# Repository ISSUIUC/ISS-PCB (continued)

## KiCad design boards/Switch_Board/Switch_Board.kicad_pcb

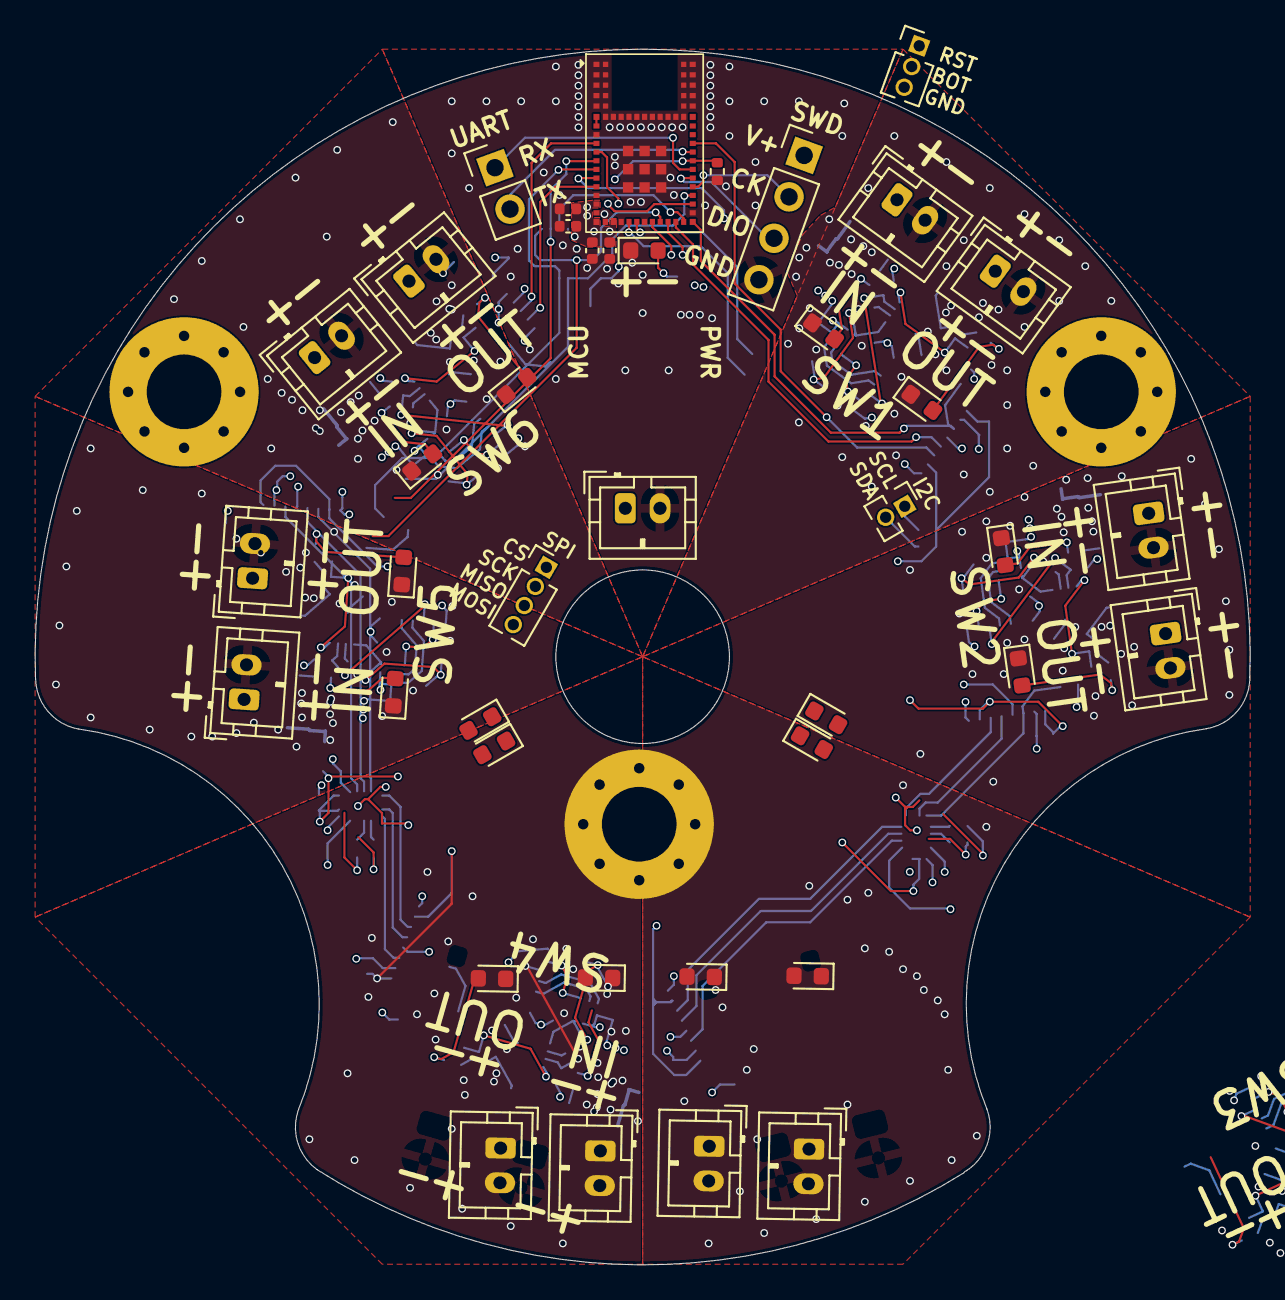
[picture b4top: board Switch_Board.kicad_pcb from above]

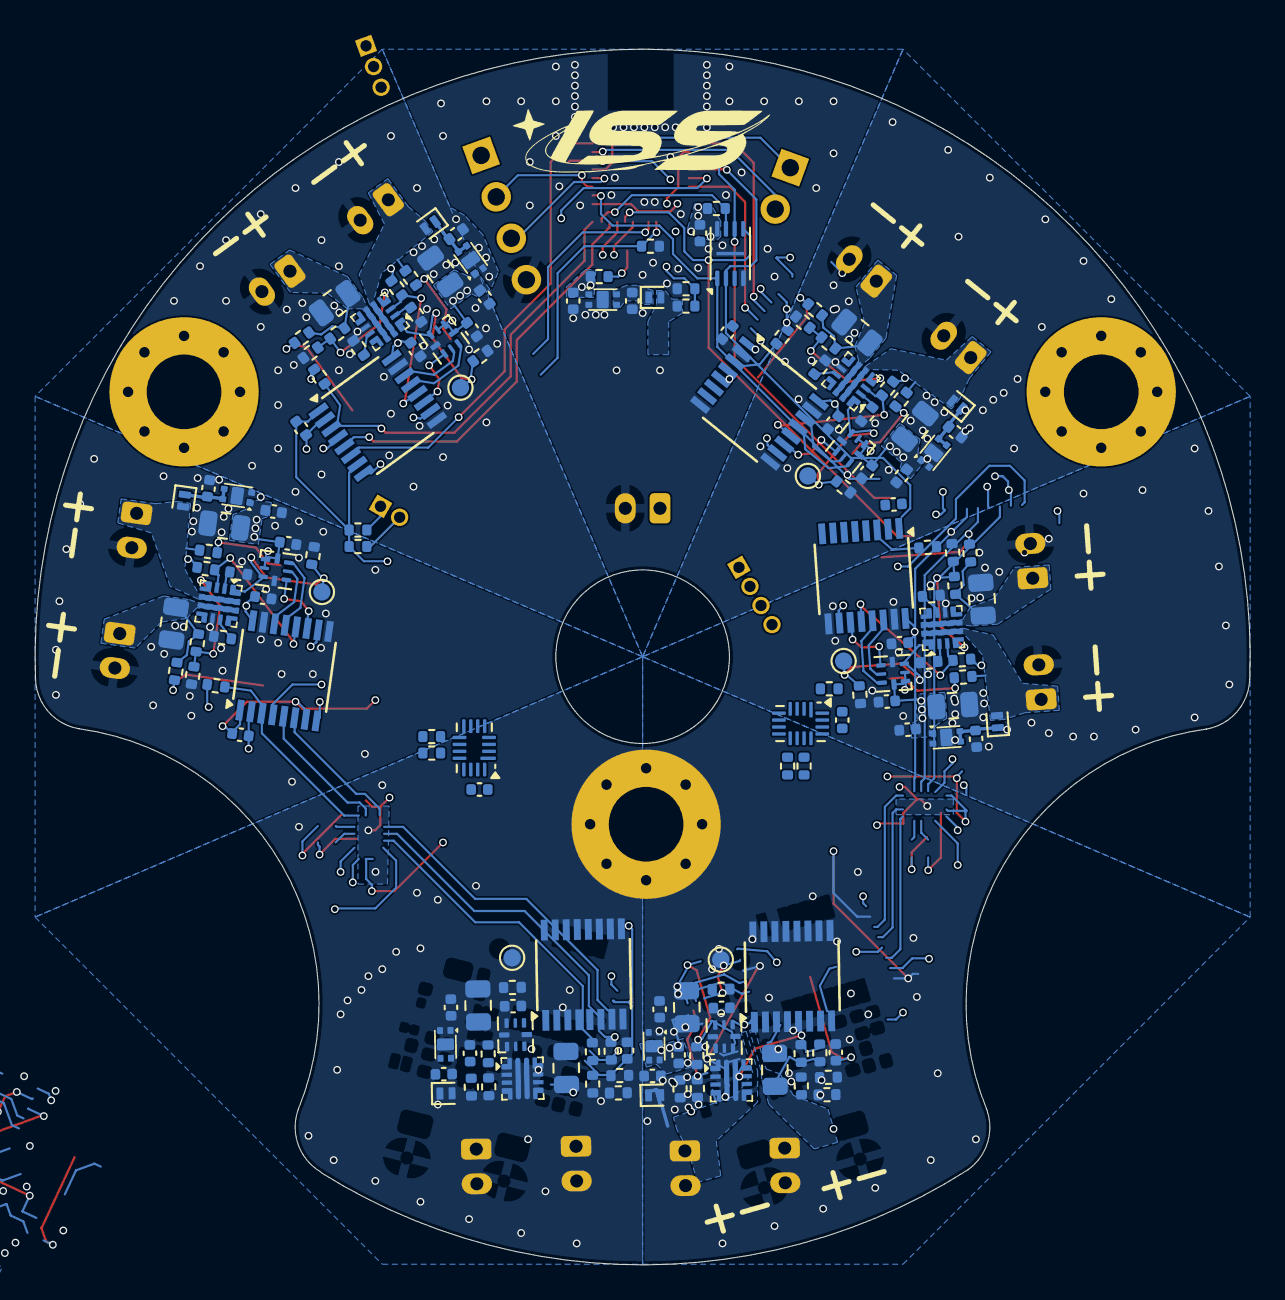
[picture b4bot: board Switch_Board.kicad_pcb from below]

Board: 4 copper layers, 70.0 x 70.0 mm, 198 parts (154 on the bottom side), 138 nets.

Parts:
C101, C103, C104, C105, C108, C109, C201, C202, C203, C301, C302, C303, C401, C402, C403, C501, C502, C503, C601, C602, C603, C701, C702, C703: 100nF; C_0402_1005Metric
C102, C107: 4.7uF; C_0402_1005Metric
C106, C204, C205, C304, C305, C404, C405, C504, C505, C604, C605, C704, C705: 1uF; C_0402_1005Metric
C206, C306, C406, C506, C606, C706: 100uF; C_0805_2012Metric
C207, C307, C407, C507, C607, C707: 22uF; C_0805_2012Metric
D101, D201, D301, D401, D501, D601, D701: SDM05U40CSP-7; D_SOD-882
D102, D103, D202, D302, D402, D502, D602, D702: RED; LED_0603_1608Metric
D104: ORANGE; LED_0603_1608Metric
D105, D203, D303, D403, D503, D603, D703: GREEN; LED_0603_1608Metric
D106: BLUE; LED_0603_1608Metric
H101, H102, H103: MountingHole_Pad; MountingHole_4.3mm_M4_Pad_Via
J101: Conn_01x03; PinHeader_1x03_P1.27mm_Vertical
J102: Conn_01x04; PinHeader_1x04_P2.54mm_Vertical
J103, J201, J203, J301, J303, J401, J403, J501, J503, J601, J603, J701, J703: Conn_01x02; JST_PH_B2B-PH-K_1x02_P2.00mm_Vertical
J104: Conn_01x02; PinHeader_1x02_P2.54mm_Vertical
J105: Conn_01x02; PinHeader_1x02_P1.27mm_Vertical
J106: Conn_01x04; PinHeader_1x04_P1.27mm_Vertical
J202, J302, J402, J502, J602, J702: Conn_01x01; TestPoint_Pad_D1.0mm
R101, R102, R103, R113, R201, R202, R204, R301, R302, R304, R401, R402, R404, R501, R502, R504, R601, R602, R604, R701, R702, R704: 10k; R_0402_1005Metric
R104, R105, R106, R107, R108: 470; R_0402_1005Metric
R109, R112: 4.7k; R_0402_1005Metric
R110, R111: 100k; R_0402_1005Metric
R203, R209, R303, R309, R403, R409, R503, R509, R603, R609, R703, R709: 1k; R_0402_1005Metric
R205, R305, R405, R505, R605, R705: 680; R_0402_1005Metric
R206, R306, R406, R506, R606, R706: 390k; R_0402_1005Metric
R207, R307, R407, R507, R607, R707: 300k; R_0402_1005Metric
R208, R308, R408, R508, R608, R708: 500k; R_0402_1005Metric
U101: W25Q16JLUX; Winbond_USON-8-1EP_3x2mm_P0.5mm_EP0.2x1.6mm
U102: STM32WB1MMC; LGA77_6P5X10_STM
U103, U203, U303, U403, U503, U603, U703: XC6223; Torex_USP-4
U104, U105: TCAL9538; UQFN-16_1.8x2.6mm_P0.4mm
U201, U301, U401, U501, U601, U701: ISO7742; SSOP-16_3.9x4.9mm_P0.635mm
U202, U302, U402, U502, U602, U702: SN74AUP1G74RSER; UQFN-RSE0008A
U204, U304, U404, U504, U604, U704: TPS25947; VQFN-HR-RPW0010A

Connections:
/BLUE_LED: R108.1, U105.10 (P7)
/BOOT: J101.2, R102.2, U102.22 (BOOT0)
/CoinCell_V: D101.2 (A), J103.1, R110.2
/EXP_RESET: R103.1, U102.13 (PA2), U104.1 (~RESET), U105.1 (~RESET)
/FLASH_CS: J106.1, U101.1 (~CS), U102.33 (PB4)
/FLASH_RESET: R101.2, U101.7 (~HOLD/~RESET/IO_{3}), U102.29 (PA7)
/GPIO_Clock: R113.2, U102.37 (PA0), U201.4 (INB), U301.4 (INB), U401.4 (INB), U501.4 (INB), U601.4 (INB), U701.4 (INB)
/GREEN_LED: R107.1, U105.9 (P6)
/I2C_SCL: J105.1, R112.1, U102.27 (PB6), U104.12 (SCL), U105.12 (SCL)
/I2C_SDA: J105.2, R109.1, U102.25 (PB7), U104.13 (SDA), U105.13 (SDA)
/NRST: J101.1, U102.23 (NRST)
/ORANGE_LED: R106.1, U104.10 (P7)
/PG_ISO_1: U102.28 (PA3), U201.5 (OUTC)
/PG_ISO_2: U104.7 (P4), U301.5 (OUTC)
/PG_ISO_3: U104.3 (P1), U401.5 (OUTC)
/PG_ISO_4: U105.7 (P4), U501.5 (OUTC)
/PG_ISO_5: U105.3 (P1), U601.5 (OUTC)
/PG_ISO_6: U102.9 (PA4), U701.5 (OUTC)
/RED_LED: R105.1, U104.9 (P6)
/SPI_MISO: J106.3, U101.2 (DO/IO_{1}), U102.12 (PA6)
/SPI_MOSI: J106.4, U101.5 (DI/IO_{0}), U102.26 (PB5)
/SPI_SCK: J106.2, U101.6 (CLK), U102.11 (PA1)
/SWCLK: J102.2, U102.34 (PA14)
/SWDIO: J102.3, U102.35 (PA13)
/Switch 1/PG: R204.2, U201.12 (INC), U204.3 (PG/AUXOFF)
/Switch 1/Q: J202.1, R202.2, U202.3 (Q), U204.1 (EN/UVLO)
/Switch 1/Reg_V: C201.1, C203.1, C205.1, C206.1, R204.1, U201.10 (EN2), U201.16 (VCC2), U202.1 (~PRE), U202.2 (~CLR), U202.8 (VCC), U203.1 (VOUT)
/Switch 1/SubBatt_GND: C201.2, C203.2, C204.2, C205.2, C206.2, C207.2, D202.1 (K), D203.1 (K), J201.2, J203.2, R202.1, R205.1, R206.2, R208.2, U201.9 (GND2), U201.15 (GND2), U202.4 (GND), U203.2 (VSS), U203.5 (EP), U204.8 (GND)
/Switch 1/SubBatt_V: D201.2 (A), J201.1, R203.1, U204.5 (IN)
/Switch 1/~Q: U201.11 (IND), U202.5 (~Q)
/Switch 2/PG: R304.2, U301.12 (INC), U304.3 (PG/AUXOFF)
/Switch 2/Q: J302.1, R302.2, U302.3 (Q), U304.1 (EN/UVLO)
/Switch 2/Reg_V: C301.1, C303.1, C305.1, C306.1, R304.1, U301.10 (EN2), U301.16 (VCC2), U302.1 (~PRE), U302.2 (~CLR), U302.8 (VCC), U303.1 (VOUT)
/Switch 2/SubBatt_GND: C301.2, C303.2, C304.2, C305.2, C306.2, C307.2, D302.1 (K), D303.1 (K), J301.2, J303.2, R302.1, R305.1, R306.2, R308.2, U301.9 (GND2), U301.15 (GND2), U302.4 (GND), U303.2 (VSS), U303.5 (EP), U304.8 (GND)
/Switch 2/SubBatt_V: D301.2 (A), J301.1, R303.1, U304.5 (IN)
/Switch 2/~Q: U301.11 (IND), U302.5 (~Q)
/Switch 3/PG: R404.2, U401.12 (INC), U404.3 (PG/AUXOFF)
/Switch 3/Q: J402.1, R402.2, U402.3 (Q), U404.1 (EN/UVLO)
/Switch 3/Reg_V: C401.1, C403.1, C405.1, C406.1, R404.1, U401.10 (EN2), U401.16 (VCC2), U402.1 (~PRE), U402.2 (~CLR), U402.8 (VCC), U403.1 (VOUT)
/Switch 3/SubBatt_GND: C401.2, C403.2, C404.2, C405.2, C406.2, C407.2, D402.1 (K), D403.1 (K), J401.2, J403.2, R402.1, R405.1, R406.2, R408.2, U401.9 (GND2), U401.15 (GND2), U402.4 (GND), U403.2 (VSS), U403.5 (EP), U404.8 (GND)
/Switch 3/SubBatt_V: D401.2 (A), J401.1, R403.1, U404.5 (IN)
/Switch 3/~Q: U401.11 (IND), U402.5 (~Q)
/Switch 4/PG: R504.2, U501.12 (INC), U504.3 (PG/AUXOFF)
/Switch 4/Q: J502.1, R502.2, U502.3 (Q), U504.1 (EN/UVLO)
/Switch 4/Reg_V: C501.1, C503.1, C505.1, C506.1, R504.1, U501.10 (EN2), U501.16 (VCC2), U502.1 (~PRE), U502.2 (~CLR), U502.8 (VCC), U503.1 (VOUT)
/Switch 4/SubBatt_GND: C501.2, C503.2, C504.2, C505.2, C506.2, C507.2, D502.1 (K), D503.1 (K), J501.2, J503.2, R502.1, R505.1, R506.2, R508.2, U501.9 (GND2), U501.15 (GND2), U502.4 (GND), U503.2 (VSS), U503.5 (EP), U504.8 (GND)
/Switch 4/SubBatt_V: D501.2 (A), J501.1, R503.1, U504.5 (IN)
/Switch 4/~Q: U501.11 (IND), U502.5 (~Q)
/Switch 5/PG: R604.2, U601.12 (INC), U604.3 (PG/AUXOFF)
/Switch 5/Q: J602.1, R602.2, U602.3 (Q), U604.1 (EN/UVLO)
/Switch 5/Reg_V: C601.1, C603.1, C605.1, C606.1, R604.1, U601.10 (EN2), U601.16 (VCC2), U602.1 (~PRE), U602.2 (~CLR), U602.8 (VCC), U603.1 (VOUT)
/Switch 5/SubBatt_GND: C601.2, C603.2, C604.2, C605.2, C606.2, C607.2, D602.1 (K), D603.1 (K), J601.2, J603.2, R602.1, R605.1, R606.2, R608.2, U601.9 (GND2), U601.15 (GND2), U602.4 (GND), U603.2 (VSS), U603.5 (EP), U604.8 (GND)
/Switch 5/SubBatt_V: D601.2 (A), J601.1, R603.1, U604.5 (IN)
/Switch 5/~Q: U601.11 (IND), U602.5 (~Q)
/Switch 6/PG: R704.2, U701.12 (INC), U704.3 (PG/AUXOFF)
/Switch 6/Q: J702.1, R702.2, U702.3 (Q), U704.1 (EN/UVLO)
/Switch 6/Reg_V: C701.1, C703.1, C705.1, C706.1, R704.1, U701.10 (EN2), U701.16 (VCC2), U702.1 (~PRE), U702.2 (~CLR), U702.8 (VCC), U703.1 (VOUT)
/Switch 6/SubBatt_GND: C701.2, C703.2, C704.2, C705.2, C706.2, C707.2, D702.1 (K), D703.1 (K), J701.2, J703.2, R702.1, R705.1, R706.2, R708.2, U701.9 (GND2), U701.15 (GND2), U702.4 (GND), U703.2 (VSS), U703.5 (EP), U704.8 (GND)
/Switch 6/SubBatt_V: D701.2 (A), J701.1, R703.1, U704.5 (IN)
/Switch 6/~Q: U701.11 (IND), U702.5 (~Q)
/Switch_1: R201.1, U102.30 (PA12), U201.3 (INA)
/Switch_2: R301.1, U104.8 (P5), U301.3 (INA)
/Switch_3: R401.1, U104.2 (P0), U401.3 (INA)
/Switch_4: R501.1, U105.8 (P5), U501.3 (INA)
/Switch_5: R601.1, U105.2 (P0), U601.3 (INA)
/Switch_6: R701.1, U102.32 (PA11), U701.3 (INA)
/UART_RX: J104.1, U102.36 (PA10)
/UART_TX: J104.2, U102.38 (PA9)
/V_SENSE: R110.1, R111.2, U102.10 (PA8)
/~Q_ISO_1: U102.39 (PA5), U201.6 (OUTD)
/~Q_ISO_2: U104.5 (P3), U301.6 (OUTD)
/~Q_ISO_3: U104.4 (P2), U401.6 (OUTD)
/~Q_ISO_4: U105.5 (P3), U501.6 (OUTD)
/~Q_ISO_5: U105.4 (P2), U601.6 (OUTD)
/~Q_ISO_6: U102.14 (PB8), U701.6 (OUTD)
MCU_GND: C101.2, C102.2, C103.2, C104.2, C105.2, C106.2, C107.2, C108.2, C109.2, C202.2, C302.2, C402.2, C502.2, C602.2, C702.2, D102.1 (K), D103.1 (K), D104.1 (K), D105.1 (K), D106.1 (K), J101.3, J102.4, J103.2, R102.1, R111.1, R113.1, R201.2, R301.2, R401.2, R501.2, R601.2, R701.2, U101.4 (GND), U101.9 (EP), U102.1 (VSS), U102.2 (VSS), U102.3 (VSS), U102.4 (VSS), U102.5 (VSSRF), U102.8 (VSSRF), U102.15 (VSS), U102.17 (VSS), U102.19 (VSS), U102.21 (VSSSMPS), U102.24 (VSS), U102.31 (VSS), U102.43 (VSS), U102.44 (VSS), U102.45 (VSS), U102.46 (VSS), U102.47 (VSS), U102.48 (VSS), U102.49 (VSS), U102.50 (VSS), U102.51 (VSS), U102.52 (VSS), U102.53 (VSS), U102.54 (VSS), U102.55 (VSS), U102.56 (VSS), U102.57 (VSS), U102.58 (VSS), U102.59 (VSS), U102.60 (VSS), U102.61 (VSS), U102.62 (VSS), U102.63 (VSS), U102.64 (VSS), U102.65 (VSS), U102.66 (VSS), U102.67 (VSS), U102.68 (VSS), U102.69 (VSS), U102.70 (VSS), U102.71 (VSS), U102.72 (VSS), U102.73 (VSS), U102.74 (VSS), U102.75 (VSS), U102.76 (VSS), U102.77 (VSS), U103.2 (VSS), U103.5 (EP), U104.6 (GND), U104.16 (A1), U105.6 (GND), U105.15 (A0), U201.2 (GND1), U201.8 (GND1), U301.2 (GND1), U301.8 (GND1), U401.2 (GND1), U401.8 (GND1), U501.2 (GND1), U501.8 (GND1), U601.2 (GND1), U601.8 (GND1), U701.2 (GND1), U701.8 (GND1)
MCU_V: C101.1, C102.1, C103.1, C104.1, C105.1, C107.1, C108.1, C109.1, C202.1, C302.1, C402.1, C502.1, C602.1, C702.1, J102.1, R101.1, R103.2, R104.2, R109.2, R112.2, U101.8 (VCC), U102.16 (VDDA), U102.18 (VBAT), U102.20 (VDDSMPS), U103.1 (VOUT), U104.14 (VCC), U104.15 (A0), U105.14 (VCC), U105.16 (A1), U201.1 (VCC1), U201.7 (EN1), U301.1 (VCC1), U301.7 (EN1), U401.1 (VCC1), U401.7 (EN1), U501.1 (VCC1), U501.7 (EN1), U601.1 (VCC1), U601.7 (EN1), U701.1 (VCC1), U701.7 (EN1)
unnamed: C106.1, D101.1 (K), U103.3 (CE), U103.4 (VIN)
unnamed: D102.2 (A), R104.1
unnamed: D103.2 (A), R105.2
unnamed: D104.2 (A), R106.2
unnamed: D105.2 (A), R107.2
unnamed: D106.2 (A), R108.2
unnamed: C204.1, D201.1 (K), U203.3 (CE), U203.4 (VIN)
unnamed: D202.2 (A), R203.2
unnamed: D203.2 (A), R209.2
unnamed: C304.1, D301.1 (K), U303.3 (CE), U303.4 (VIN)
unnamed: D302.2 (A), R303.2
unnamed: D303.2 (A), R309.2
unnamed: C404.1, D401.1 (K), U403.3 (CE), U403.4 (VIN)
unnamed: D402.2 (A), R403.2
unnamed: D403.2 (A), R409.2
unnamed: C504.1, D501.1 (K), U503.3 (CE), U503.4 (VIN)
unnamed: D502.2 (A), R503.2
unnamed: D503.2 (A), R509.2
unnamed: C604.1, D601.1 (K), U603.3 (CE), U603.4 (VIN)
unnamed: D602.2 (A), R603.2
unnamed: D603.2 (A), R609.2
unnamed: C704.1, D701.1 (K), U703.3 (CE), U703.4 (VIN)
unnamed: D702.2 (A), R703.2
unnamed: D703.2 (A), R709.2
unnamed: C207.1, J203.1, R207.1, R209.1, U204.6 (OUT)
unnamed: C307.1, J303.1, R307.1, R309.1, U304.6 (OUT)
unnamed: C407.1, J403.1, R407.1, R409.1, U404.6 (OUT)
unnamed: C507.1, J503.1, R507.1, R509.1, U504.6 (OUT)
unnamed: C607.1, J603.1, R607.1, R609.1, U604.6 (OUT)
unnamed: C707.1, J703.1, R707.1, R709.1, U704.6 (OUT)
unnamed: U102.6 (ANT_IN), U102.7 (ANT_OUT)
unnamed: U201.14 (OUTA), U202.6 (D)
unnamed: U201.13 (OUTB), U202.7 (CLK)
unnamed: R205.2, U204.9 (ILM)
unnamed: R206.1, U204.2 (OVLO/OVCSEL)
unnamed: R207.2, R208.1, U204.4 (PGTH/NFLT)
unnamed: U301.14 (OUTA), U302.6 (D)
unnamed: U301.13 (OUTB), U302.7 (CLK)
unnamed: R305.2, U304.9 (ILM)
unnamed: R306.1, U304.2 (OVLO/OVCSEL)
unnamed: R307.2, R308.1, U304.4 (PGTH/NFLT)
unnamed: U401.14 (OUTA), U402.6 (D)
unnamed: U401.13 (OUTB), U402.7 (CLK)
unnamed: R405.2, U404.9 (ILM)
unnamed: R406.1, U404.2 (OVLO/OVCSEL)
unnamed: R407.2, R408.1, U404.4 (PGTH/NFLT)
unnamed: U501.14 (OUTA), U502.6 (D)
unnamed: U501.13 (OUTB), U502.7 (CLK)
unnamed: R505.2, U504.9 (ILM)
unnamed: R506.1, U504.2 (OVLO/OVCSEL)
unnamed: R507.2, R508.1, U504.4 (PGTH/NFLT)
unnamed: U601.14 (OUTA), U602.6 (D)
unnamed: U601.13 (OUTB), U602.7 (CLK)
unnamed: R605.2, U604.9 (ILM)
unnamed: R606.1, U604.2 (OVLO/OVCSEL)
unnamed: R607.2, R608.1, U604.4 (PGTH/NFLT)
unnamed: U701.14 (OUTA), U702.6 (D)
unnamed: U701.13 (OUTB), U702.7 (CLK)
unnamed: R705.2, U704.9 (ILM)
unnamed: R706.1, U704.2 (OVLO/OVCSEL)
unnamed: R707.2, R708.1, U704.4 (PGTH/NFLT)
